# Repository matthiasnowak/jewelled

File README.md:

# JewelLED / LuxAura Earring

These stylish earrings have 18 small LEDs on them, which can light up in any pattern. A microphone allows for the potential to sync the patterns up to music. The whole earring is powered off a regular coin cell battery, and can even be used with lithium rechargeable coin cells! It runs around 10-12h at moderate animation load and brightness of a LIR2032 rechargeable Lithium battery

A seperate charging and programming board allows to interface the earrings with your PC, gives you simple access to the programming pin of the earrings and can be used to charge them up if used with lithium rechargeable coin cells.

## Hardware Overview:

### LuxAura 01:

- WCH CH32V203G6U6 microcontroller
- 18 LEDs 0603, single color
- CR2032 battery holder
- optional LIR2032 charging and protection circuit
- Operating at 2.7V, allowing for low battery voltage operation
- 2 buttons and a power switch
- buzzer for audio user feedback
- microphone, which can be used for music detection

### LuxCharge:

- TBD

## Software

Software is currently WIP. The charging board can activate/deactivate 5V charging voltage to the earrings and can rudimentely detect their presence.
The earring software can show basic animations and cycle between them. Test code for microphone sampling is running, but currently beat detection doesnt work.

## Ressources and other notes

- Images, schematics and PCB plots can be found in the "res" folder.
- Development is published here, issues are used for internal issue and project tracking. Feel free to contribute
- The PCBs can be ordered through Turnkey PCBA providers like JLCPCB.

## License

The attached LICENSE.md file contains information about the license.

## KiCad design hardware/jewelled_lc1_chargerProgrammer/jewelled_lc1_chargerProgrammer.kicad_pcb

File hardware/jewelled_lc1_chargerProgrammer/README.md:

# LuxAura LuxCharger Hardware

## Hardware Overview

- WIP

## Notes

- WIP
- Please note the correct jumper settings to allow communications or setting pullup/down resistors

## Images

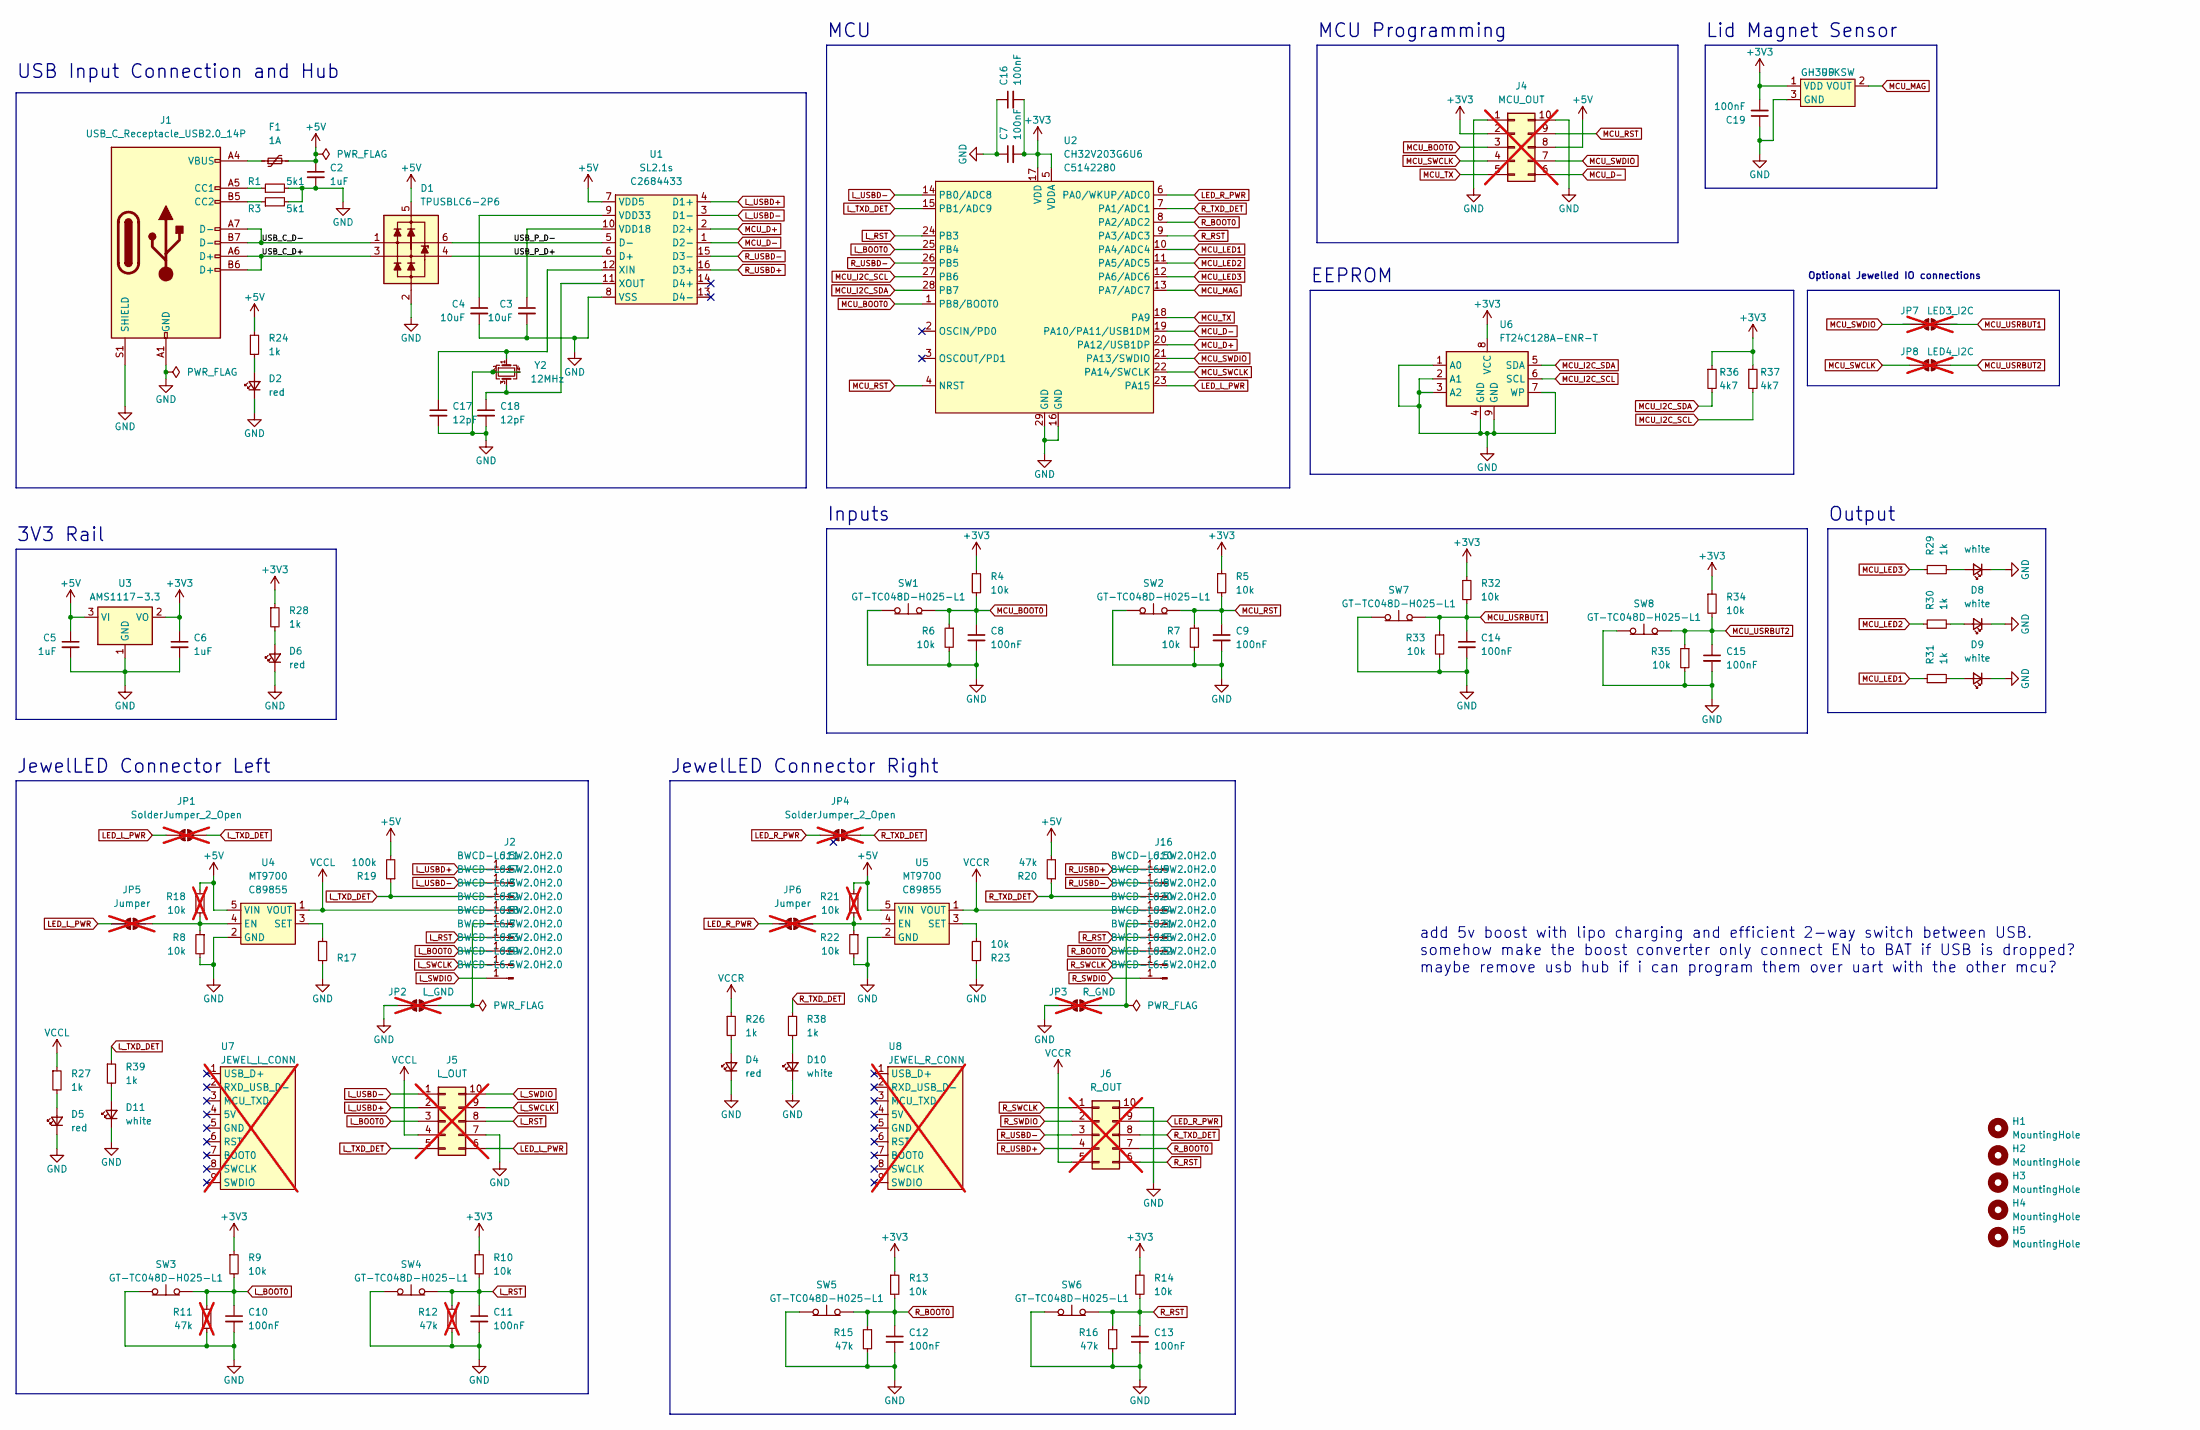
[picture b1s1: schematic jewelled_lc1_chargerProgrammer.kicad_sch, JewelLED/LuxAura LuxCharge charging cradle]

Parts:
C2, C5, C6: 1uF; C_0603_1608Metric; MPN C15849; LCSC C15849
C3, C4: 10uF; C_0805_2012Metric; MPN C19702; LCSC C19702
C7, C8, C9, C10, C11, C12, C13, C14, C15, C16, C19: 100nF; C_0603_1608Metric; MPN C14663; LCSC C14663
C17, C18: 12pF; C_0603_1608Metric; MPN C38523; LCSC C38523
D1: TPUSBLC6-2P6; SOT-666; MPN C2682291; LCSC C2682291
D2, D4, D5, D6: red; LED_0603_1608Metric; MPN C2286; LCSC C2286
D7, D8, D9, D10, D11: white; LED_0603_1608Metric; MPN C2290; LCSC C2290
F1: 1A; Fuse_1210_3225Metric; MPN C692151; LCSC C692151
H1, H2, H3, H4, H5: MountingHole; Mounting_Sinhoo-M2_H2mm_SMTSO2020MTJ; MPN C2916384; LCSC C2916384
J1: USB_C_Receptacle_USB2.0_14P; USB_C_Receptacle_GT-USB-7010B; MPN C2988369; LCSC C2988369
J2, J3, J7, J8, J9, J10, J11, J12, J13, J14, J15, J16, J17, J18, J19, J20, J21, J22: BWCD-L6.5W2.0H2.0; jewelled_2mm_pogopad; MPN C2826552; LCSC C2826552
J4: MCU_OUT; pogoheader_2x05_1.5mm; MPN x; not fitted
J5: L_OUT; pogoheader_2x05_1.5mm; MPN x; not fitted
J6: R_OUT; pogoheader_2x05_1.5mm; MPN x; not fitted
JP1, JP4: SolderJumper_2_Open; SolderJumper-2_P1.3mm_Open_RoundedPad1.0x1.5mm; MPN x; not fitted
JP2: L_GND; SolderJumper-2_P1.3mm_Open_RoundedPad1.0x1.5mm; MPN x; not fitted
JP3: R_GND; SolderJumper-2_P1.3mm_Open_RoundedPad1.0x1.5mm; MPN x; not fitted
JP5, JP6: Jumper; SolderJumper-2_P1.3mm_Open_RoundedPad1.0x1.5mm; MPN x; not fitted
JP7: LED3_I2C; SolderJumper-2_P1.3mm_Open_RoundedPad1.0x1.5mm; MPN x; not fitted
JP8: LED4_I2C; SolderJumper-2_P1.3mm_Open_RoundedPad1.0x1.5mm; MPN x; not fitted
R1, R3: 5k1; R_0603_1608Metric; MPN C23186; LCSC C23186
R4, R5, R6, R7, R8, R9, R10, R13, R14, R17, R22, R23, R32, R33, R34, R35: 10k; R_0603_1608Metric; MPN C25804; LCSC C25804
R11, R12: 47k; R_0603_1608Metric; MPN C25819; LCSC C25819; not fitted
R15, R16, R20: 47k; R_0603_1608Metric; MPN C25819; LCSC C25819
R18, R21: 10k; R_0603_1608Metric; MPN C25804; LCSC C25804; not fitted
R19: 100k; R_0603_1608Metric; MPN C25803; LCSC C25803
R24, R26, R27, R28, R29, R30, R31, R38, R39: 1k; R_0603_1608Metric; MPN C21190; LCSC C21190
R36, R37: 4k7; R_0603_1608Metric; MPN C23162; LCSC C23162
SW1, SW2, SW3, SW4, SW5, SW6, SW7, SW8: GT-TC048D-H025-L1; MPN C843674; LCSC C843674
U1: SL2.1s; SSOP16_SL2.1S; MPN C2684433; LCSC C2684433
U2: CH32V203G6U6; QFN-28-1EP_4x4mm_P0.4mm_EP2.6x2.6mm; MPN C5142280; LCSC C5142280
U3: AMS1117-3.3; SOT-89-3; MPN C18723569; LCSC C18723569
U4, U5: MT9700; SOT-23-5; MPN C89855; LCSC C89855
U6: FT24C128A-ENR-T; DFN-8-1EP_3x2mm_P0.5mm_EP1.7x1.6mm; MPN C232872; LCSC C232872
U7: JEWEL_L_CONN; jewelled_lc1_v1_conn; MPN C2826552; LCSC C2826552; not fitted
U8: JEWEL_R_CONN; jewelled_lc1_v1_conn; MPN C2826552; LCSC C2826552; not fitted
U9: GH39FKSW; SOT-23-3; MPN C266230; LCSC C266230
Y2: 12MHz; Crystal_SMD_2520-4Pin_2.5x2.0mm; MPN C5122639; LCSC C5122639

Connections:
+3V3: C6.1, C7.2, C16.2, C19.2, J4.2, R4.1, R5.1, R9.1, R10.1, R13.1, R14.1, R28.1, R32.1, R34.1, R36.1, R37.1, U2.5 (VDDA), U2.17 (VDD), U3.2 (VO), U6.8 (VCC), U9.1 (VDD)
+5V: C2.1, C5.1, D1.5 (VP), F1.2, J4.8, R18.1, R19.2, R20.2, R21.1, R24.1, U1.7 (VDD5), U3.3 (VI), U4.5 (VIN), U5.5 (VIN)
/USB_C_D+: D1.3 (L2), J1.A6 (D+), J1.B6 (D+)
/USB_C_D-: D1.1 (L1), J1.A7 (D-), J1.B7 (D-)
/USB_P_D+: D1.4 (L2), U1.6 (D+)
/USB_P_D-: D1.6 (L1), U1.5 (D-)
GND: C2.2, C3.2, C4.2, C5.2, C6.2, C7.1, C8.2, C9.2, C10.2, C11.2, C12.2, C13.2, C14.2, C15.2, C16.1, C17.2, C18.2, C19.1, D1.2 (VN), D2.1 (K), D4.1 (K), D5.1 (K), D6.1 (K), D7.1 (K), D8.1 (K), D9.1 (K), D10.1 (K), D11.1 (K), J1.A1 (GND), J1.A12 (GND), J1.B1 (GND), J1.B12 (GND), J1.S1 (SHIELD), J4.1, J4.10, J5.7, J6.10, JP2.2 (B), JP3.2 (B), R1.2, R3.2, R6.2, R7.2, R8.2, R11.2, R12.2, R15.2, R16.2, R17.1, R22.2, R23.1, R33.2, R35.2, SW1.1 (A), SW2.1 (A), SW3.1 (A), SW4.1 (A), SW5.1 (A), SW6.1 (A), SW7.1 (A), SW8.1 (A), U1.8 (VSS), U2.16 (GND), U2.29 (GND), U3.1 (GND), U4.2 (GND), U5.2 (GND), U6.1 (A0), U6.2 (A1), U6.3 (A2), U6.4 (GND), U6.7 (WP), U6.9 (GND), U9.3 (GND), Y2.2, Y2.4
LED_L_PWR: J5.6, JP1.1 (A), JP5.1 (A), U2.23 (PA15)
LED_R_PWR: J6.9, JP4.1 (A), JP6.1 (A), U2.6 (PA0/WKUP/ADC0)
L_BOOT0: C10.1, J5.3, J7.1, R9.2, R11.1, SW3.2 (B), U2.25 (PB4)
L_RST: C11.1, J5.8, J18.1, R10.2, R12.1, SW4.2 (B), U2.24 (PB3)
L_SWCLK: J5.9, J13.1
L_SWDIO: J5.10, J19.1
L_TXD_DET: J5.5, J17.1, JP1.2 (B), R19.1, R39.1, U2.15 (PB1/ADC9)
L_USBD+: J2.1, J5.2, U1.4 (D1+)
L_USBD-: J5.1, J11.1, U1.3 (D1-), U2.14 (PB0/ADC8)
MCU_BOOT0: C8.1, J4.3, R4.2, R6.1, SW1.2 (B), U2.1 (PB8/BOOT0)
MCU_D+: U1.2 (D2+), U2.20 (PA12/USB1DP)
MCU_D-: J4.6, U1.1 (D2-), U2.19 (PA10/PA11/USB1DM)
MCU_I2C_SCL: R37.2, U2.27 (PB6), U6.6 (SCL)
MCU_I2C_SDA: R36.2, U2.28 (PB7), U6.5 (SDA)
MCU_LED1: R31.1, U2.10 (PA4/ADC4)
MCU_LED2: R30.1, U2.11 (PA5/ADC5)
MCU_LED3: R29.1, U2.12 (PA6/ADC6)
MCU_MAG: U2.13 (PA7/ADC7), U9.2 (VOUT)
MCU_RST: C9.1, J4.9, R5.2, R7.1, SW2.2 (B), U2.4 (NRST)
MCU_SWCLK: J4.4, JP8.2 (B), U2.22 (PA14/SWCLK)
MCU_SWDIO: J4.7, JP7.2 (B), U2.21 (PA13/SWDIO)
MCU_TX: J4.5, U2.18 (PA9)
MCU_USRBUT1: C14.1, JP7.1 (A), R32.2, R33.1, SW7.2 (B)
MCU_USRBUT2: C15.1, JP8.1 (A), R34.2, R35.1, SW8.2 (B)
unnamed: D2.2 (A), R24.2
unnamed: D4.2 (A), R26.2
unnamed: D5.2 (A), R27.2
unnamed: D6.2 (A), R28.2
unnamed: D7.2 (A), R29.2
unnamed: D8.2 (A), R30.2
unnamed: D9.2 (A), R31.2
unnamed: D10.2 (A), R38.2
unnamed: D11.2 (A), R39.2
unnamed: F1.1, J1.A4 (VBUS), J1.A9 (VBUS), J1.B4 (VBUS), J1.B9 (VBUS)
unnamed: J1.A5 (CC1), R1.1
unnamed: J1.B5 (CC2), R3.1
unnamed: J12.1, JP2.1 (A)
unnamed: J20.1, JP3.1 (A)
unnamed: JP5.2 (B), R8.1, R18.2, U4.4 (EN)
unnamed: JP6.2 (B), R21.2, R22.1, U5.4 (EN)
unnamed: C3.1, U1.10 (VDD18)
unnamed: C4.1, U1.9 (VDD33)
unnamed: C17.1, U1.12 (XIN), Y2.1
unnamed: C18.1, U1.11 (XOUT), Y2.3
unnamed: R17.2, U4.3 (SET)
unnamed: R23.2, U5.3 (SET)
R_BOOT0: C12.1, J6.7, J21.1, R13.2, R15.1, SW5.2 (B), U2.8 (PA2/ADC2)
R_RST: C13.1, J6.6, J14.1, R14.2, R16.1, SW6.2 (B), U2.9 (PA3/ADC3)
R_SWCLK: J6.1, J15.1
R_SWDIO: J6.2, J22.1
R_TXD_DET: J6.8, J9.1, JP4.2 (B), R20.1, R38.1, U2.7 (PA1/ADC1)
R_USBD+: J6.4, J16.1, U1.16 (D3+)
R_USBD-: J6.3, J10.1, U1.15 (D3-), U2.26 (PB5)
VCCL: J3.1, J5.4, R27.1, U4.1 (VOUT)
VCCR: J6.5, J8.1, R26.1, U5.1 (VOUT)

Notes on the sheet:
3V3 Rail
JewelLED Connector Left
JewelLED Connector Right
EEPROM
Optional Jewelled IO connections
Inputs
USB Input Connection and Hub
MCU
MCU Programming
add 5v boost with lipo charging and efficient 2-way switch between USB. somehow make the boost converter only connect EN to BAT if USB is dropped? maybe remove usb hub if i can program them over uart with the other mcu?
Lid Magnet Sensor
Output

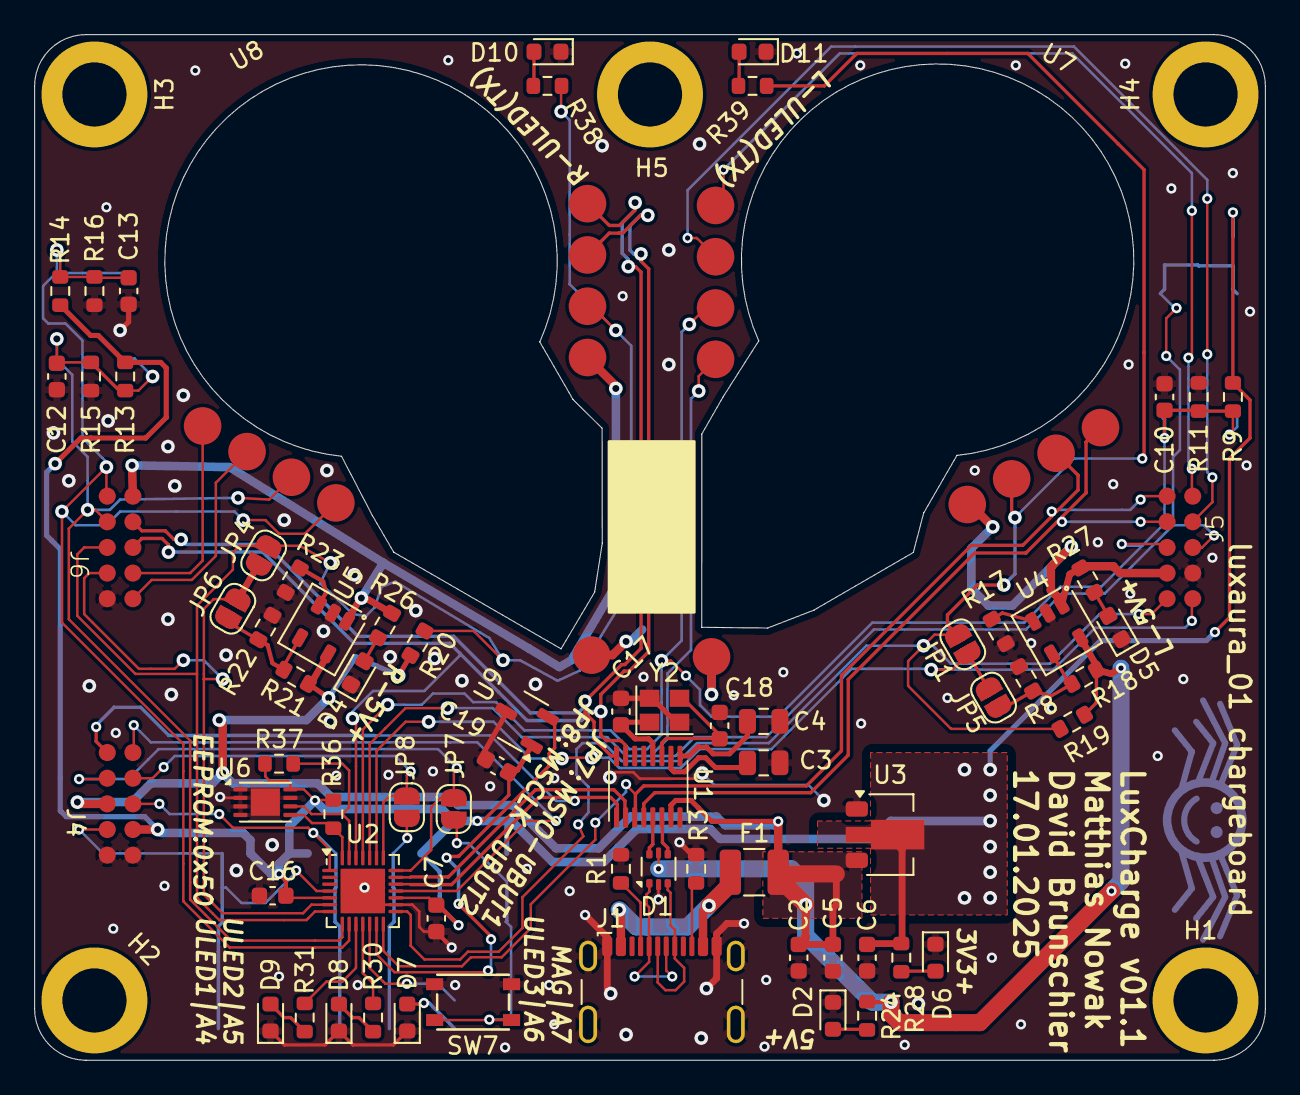
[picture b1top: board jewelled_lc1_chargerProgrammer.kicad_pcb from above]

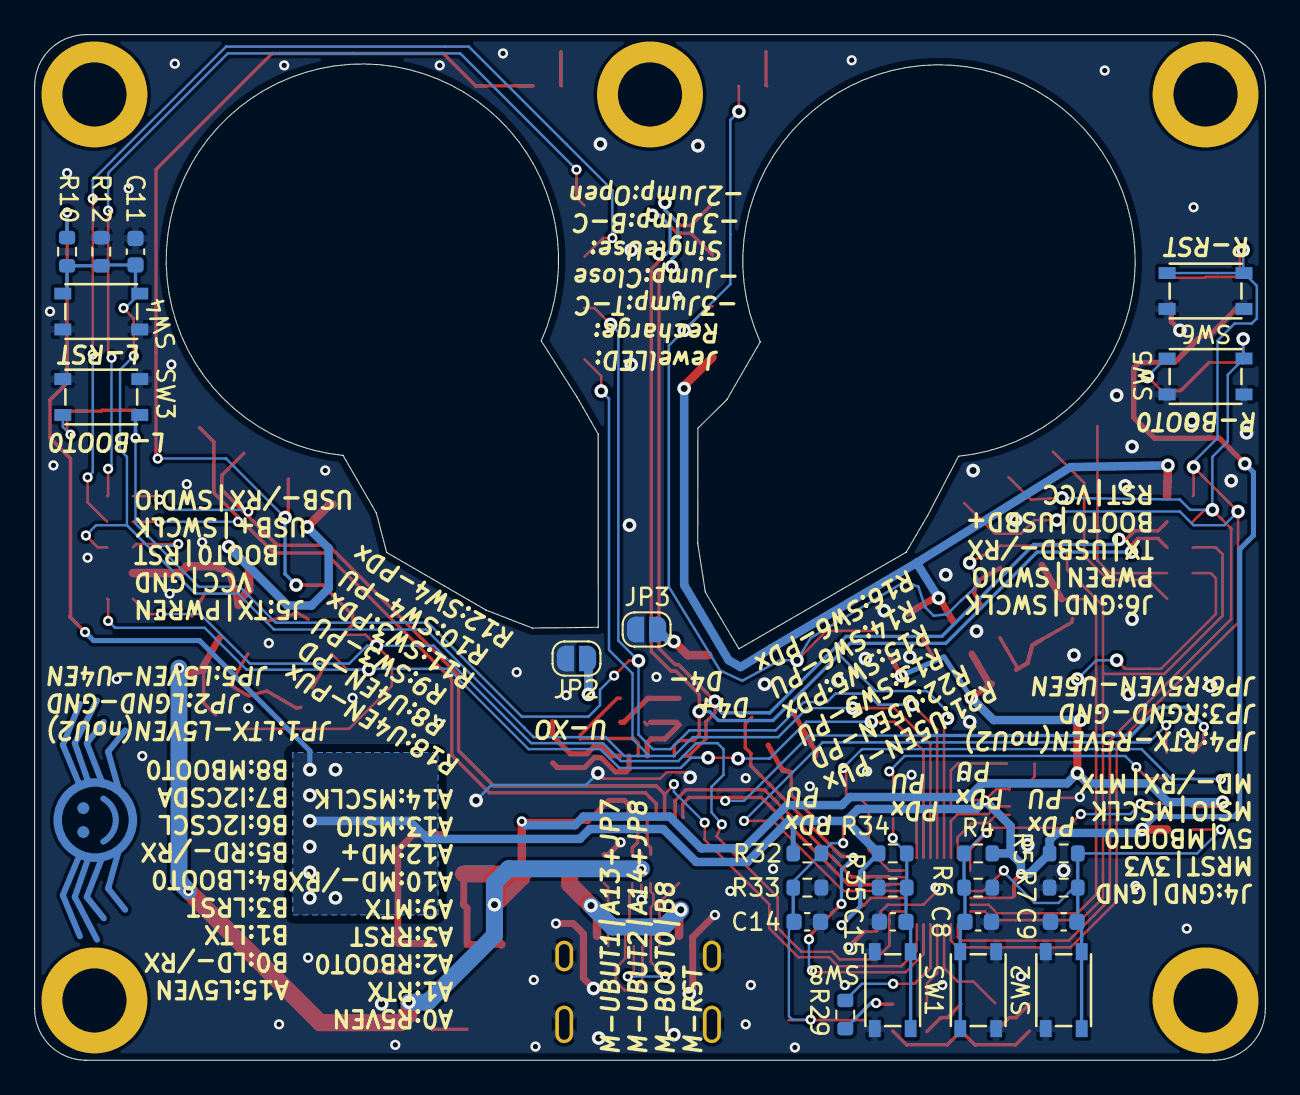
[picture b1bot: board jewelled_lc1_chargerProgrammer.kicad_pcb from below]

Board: 2 copper layers, 72.0 x 60.0 mm, 119 parts (25 on the bottom side), 62 nets.

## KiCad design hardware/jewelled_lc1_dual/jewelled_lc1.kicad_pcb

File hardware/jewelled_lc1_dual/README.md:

# LuxAura 01 Dual Earring Hardware

## Notes

This is a panel meant for production of the Earrings, allowing for 2 Earrings per panel.

## Images

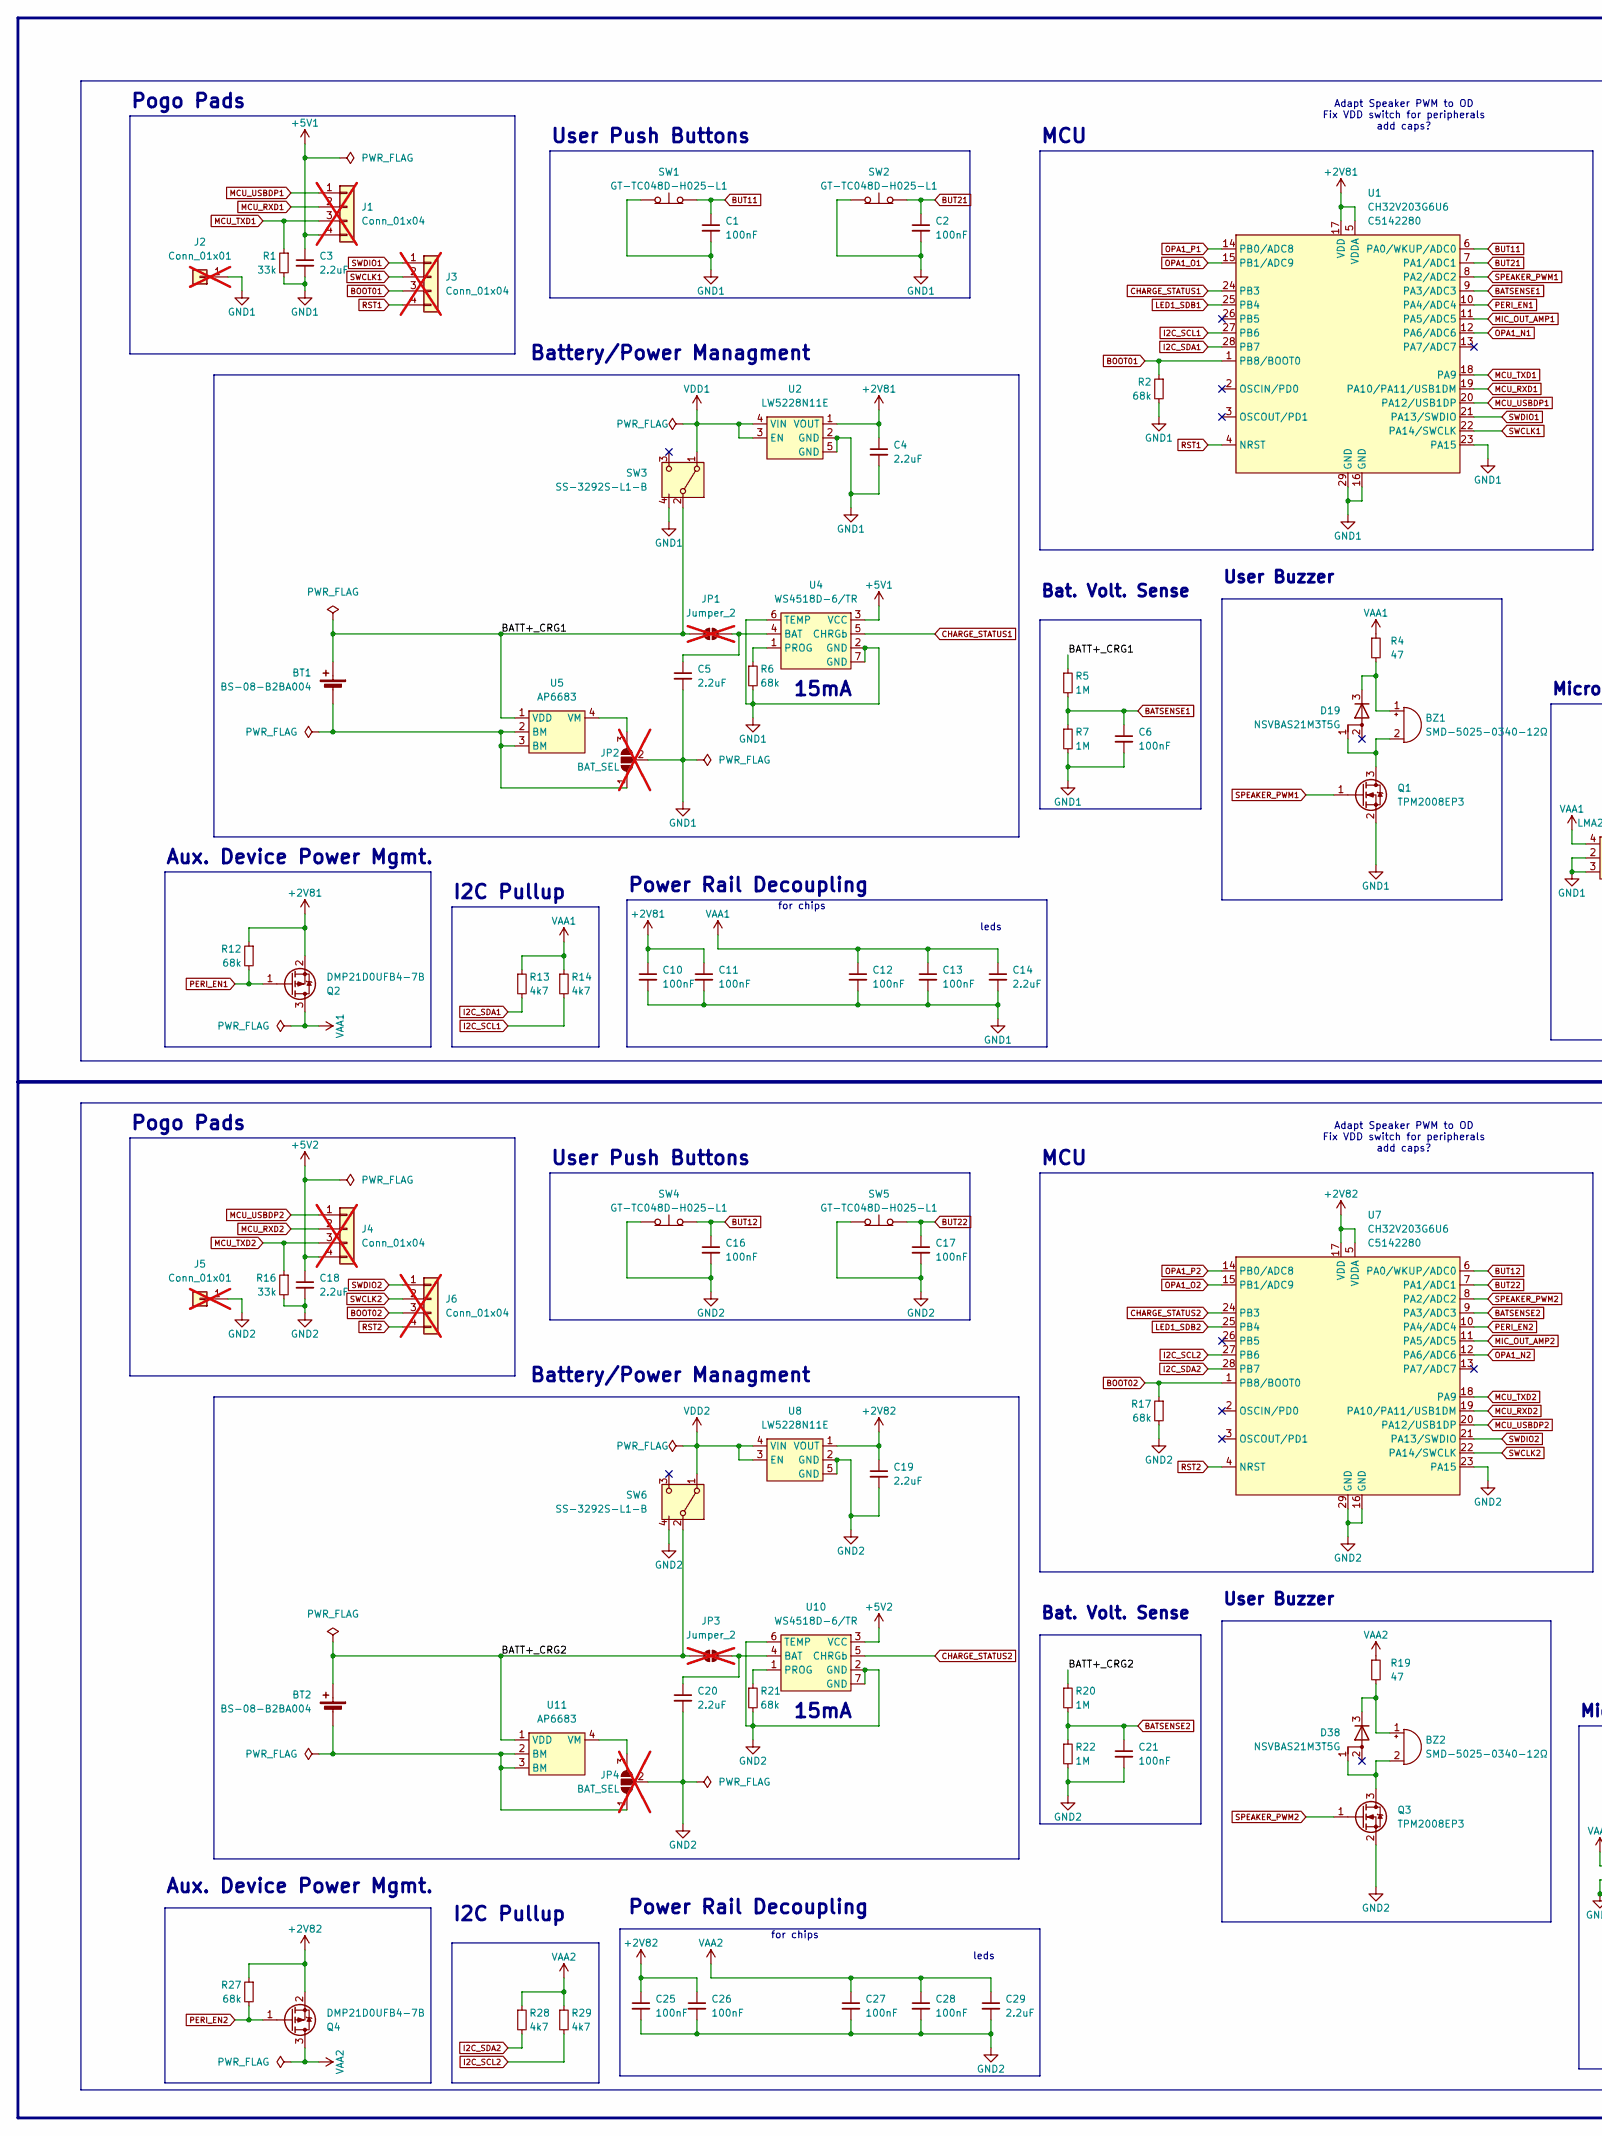
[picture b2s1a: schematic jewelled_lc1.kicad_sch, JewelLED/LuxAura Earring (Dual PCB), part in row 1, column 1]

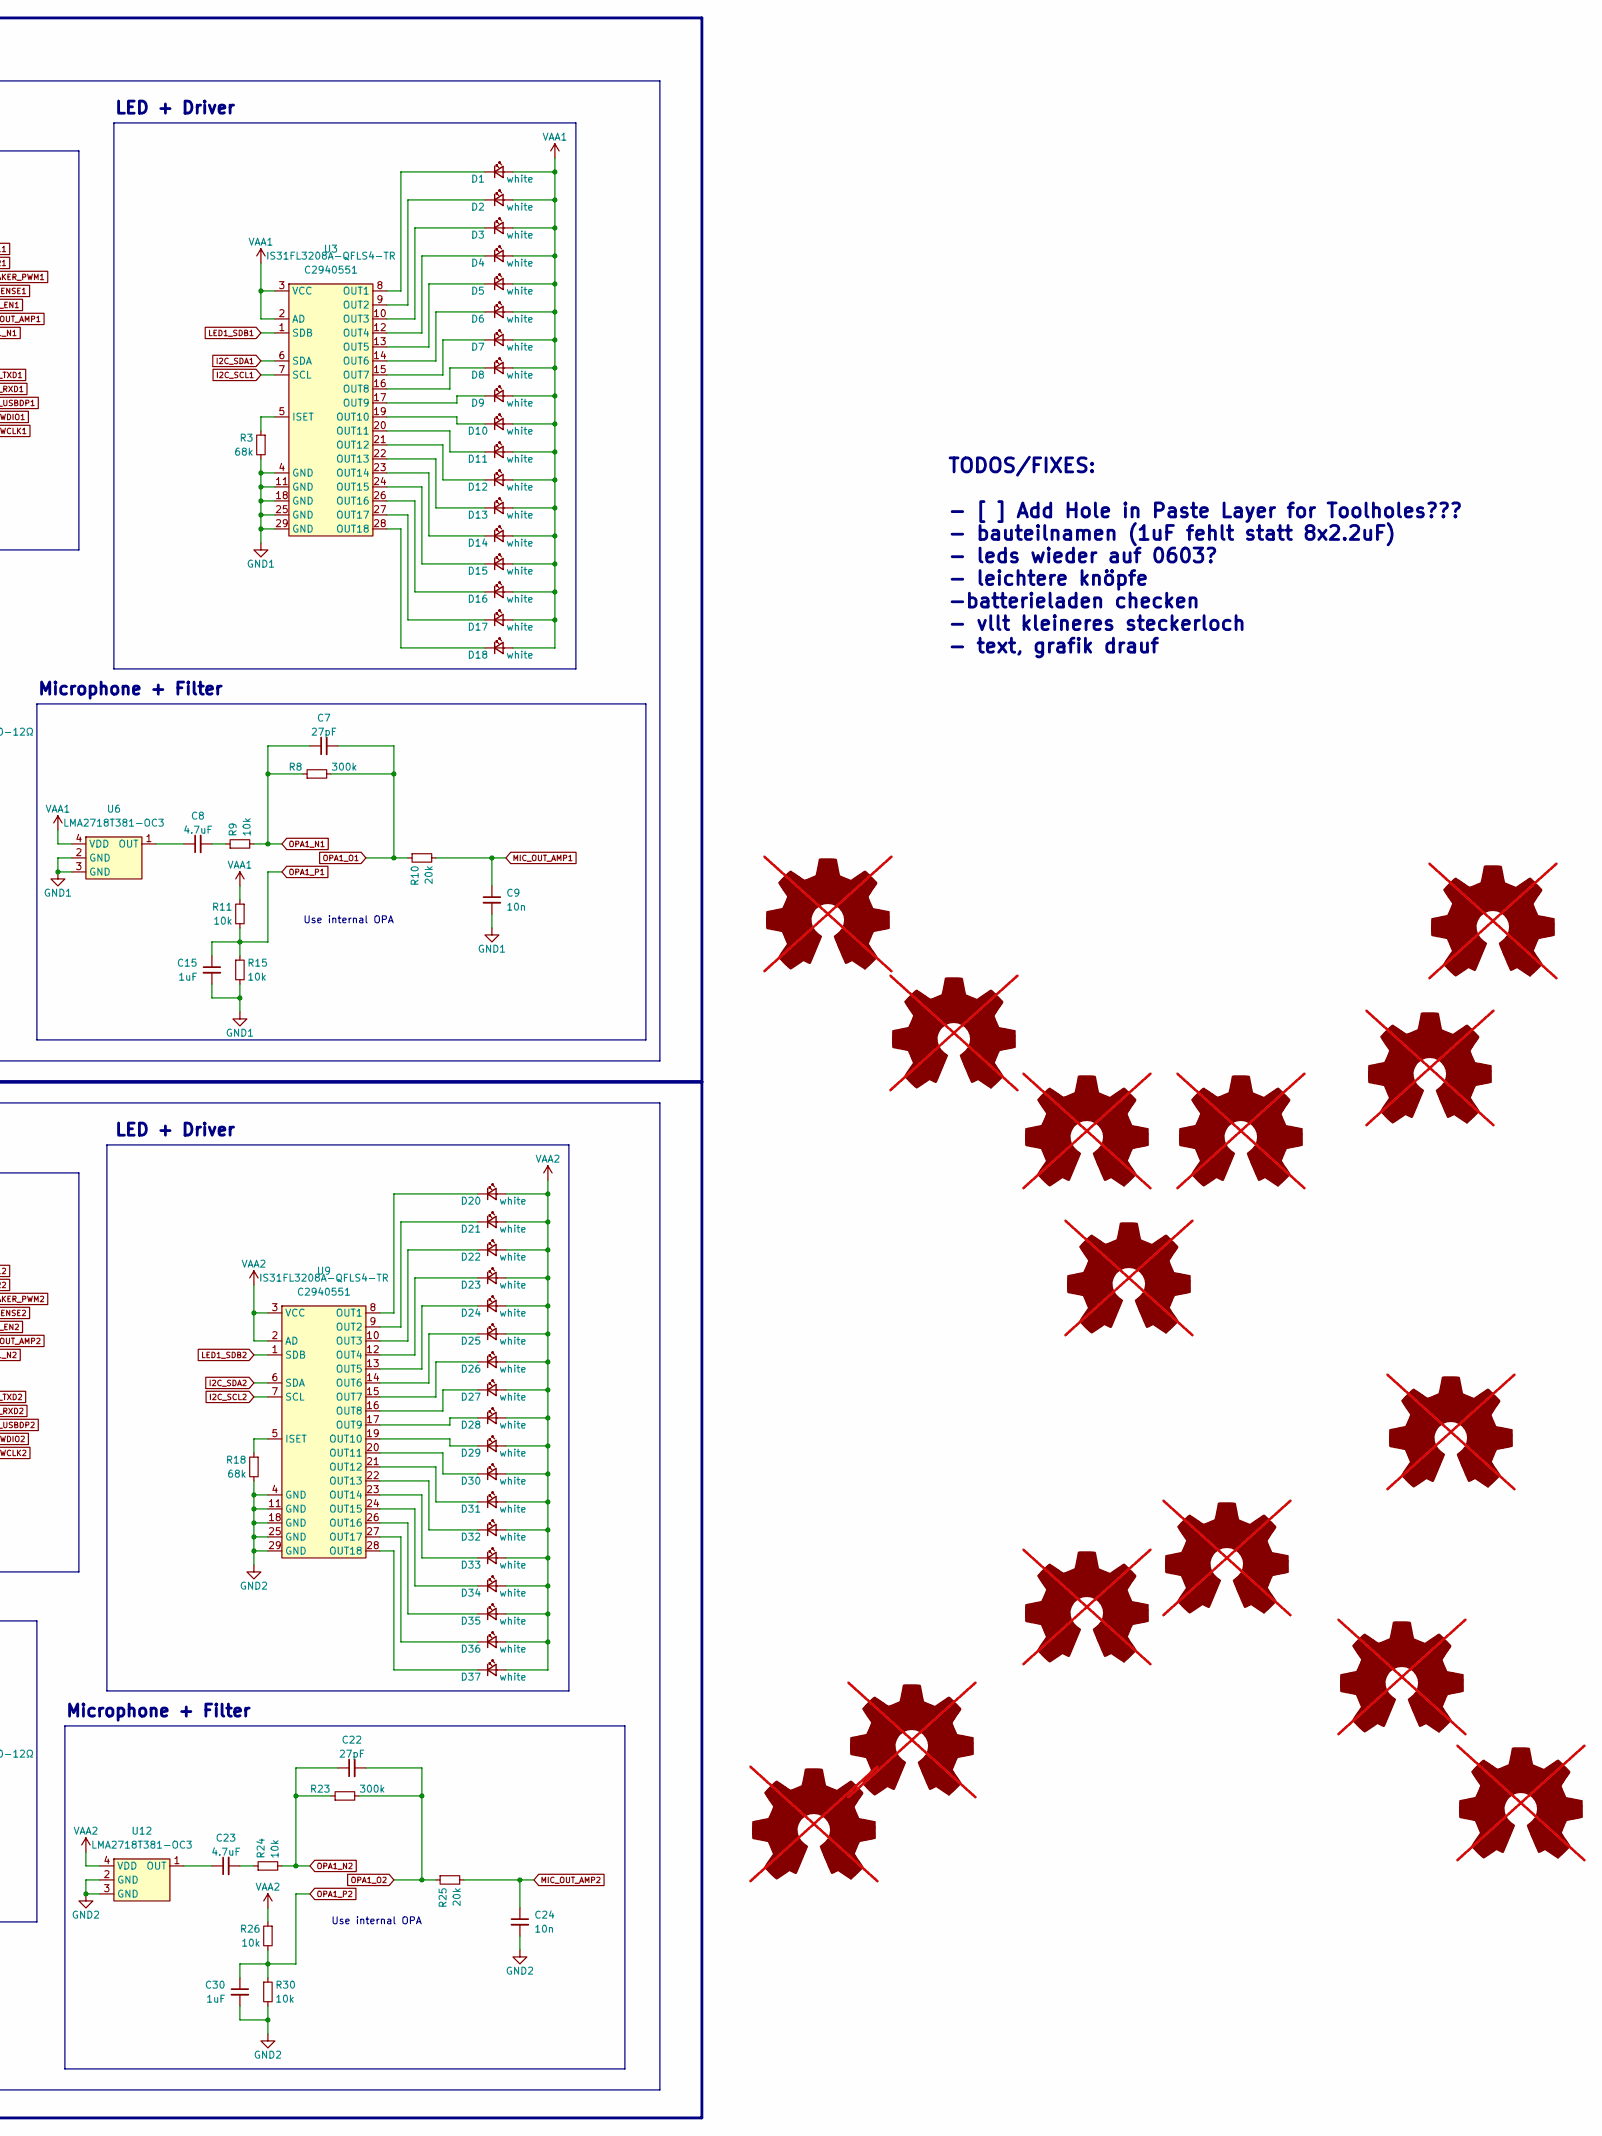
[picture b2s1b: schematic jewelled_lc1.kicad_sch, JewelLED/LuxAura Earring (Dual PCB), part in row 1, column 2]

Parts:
BT1, BT2: BS-08-B2BA004; MPN C964780; LCSC C964780
BZ1, BZ2: SMD-5025-0340-12Ω; SMD-5025-0340; MPN C2693575; LCSC C2693575
C1, C2, C6, C10, C11, C12, C13, C16, C17, C21, C25, C26, C27, C28: 100nF; C_0402_1005Metric; MPN C1525; LCSC C1525
C3, C4, C5, C14, C18, C19, C20, C29: 2.2uF; C_0402_1005Metric; MPN C12530; LCSC C12530
C7, C22: 27pF; C_0402_1005Metric; MPN C1557; LCSC C1557
C8, C23: 4.7uF; C_0402_1005Metric; MPN C23733; LCSC C23733
C9, C24: 10n; C_0402_1005Metric; MPN C15195; LCSC C15195
C15, C30: 1uF; C_0402_1005Metric; MPN C52923; LCSC C52923
D1, D2, D3, D4, D5, D6, D7, D8, D9, D10, D11, D12, D13, D14, D15, D16, D17, D18, D20, D21, D22, D23, D24, D25, D26, D27, D28, D29, D30, D31, D32, D33, D34, D35, D36, D37: white; LED_0402_1005Metric; MPN C157742; LCSC C157742
D19, D38: NSVBAS21M3T5G; SOT-723; MPN C896450; LCSC C896450
J1, J3, J4, J6: Conn_01x04; pogo_conn_01x03_P2.0mm_angled; not fitted
J2, J5: Conn_01x01; pogo_conn_01x01_P2.0mm; not fitted
JP1, JP3: Jumper_2; SolderJumper-2_P1.3mm_Open_RoundedPad1.0x1.5mm_NoSilk; not fitted
JP2, JP4: BAT_SEL; SolderJumper-3_P1.3mm_Open_RoundedPad1.0x1.5mm_NoSilk; not fitted
Q1, Q3: TPM2008EP3; DFN-3_1.0x0.6mm_P0.35mm; MPN C2682293; LCSC C2682293
Q2, Q4: DMP21D0UFB4-7B; DFN-3_1.0x0.6mm_P0.35mm; MPN C155329; LCSC C155329
R1, R16: 33k; R_0402_1005Metric; MPN C25779; LCSC C25779
R2, R3, R6, R12, R17, R18, R21, R27: 68k; R_0402_1005Metric; MPN C36871; LCSC C36871
R4, R19: 47; R_0402_1005Metric; MPN C25118; LCSC C25118
R5, R7, R20, R22: 1M; R_0402_1005Metric; MPN C26083; LCSC C26083
R8, R23: 300k; R_0402_1005Metric; MPN C25774; LCSC C25774
R9, R11, R15, R24, R26, R30: 10k; R_0402_1005Metric; MPN C25744; LCSC C25744
R10, R25: 20k; R_0402_1005Metric; MPN C25765; LCSC C25765
R13, R14, R28, R29: 4k7; R_0402_1005Metric; MPN C25900; LCSC C25900
SW1, SW2, SW4, SW5: GT-TC048D-H025-L1; MPN C843674; LCSC C843674
SW3, SW6: SS-3292S-L1-B; MPN C397350; LCSC C397350
SYM1, SYM2, SYM13, SYM14: jlcpcb_toolhole; not fitted
SYM3, SYM4, SYM11, SYM12: jlcpcb_fiducial; Fiducial_1mm_Mask2mm; not fitted
SYM5, SYM6, SYM9, SYM10: mousebite_outer; not fitted
SYM7, SYM8: mousebite_inner; not fitted
U1, U7: CH32V203G6U6; QFN-28-1EP_4x4mm_P0.4mm_EP2.6x2.6mm; MPN C5142280; LCSC C5142280
U2, U8: LW5228N11E; UDFN-4-1EP_1x1mm_P0.65mm_EP0.48x0.48mm; MPN C20630428; LCSC C20630428
U3, U9: IS31FL3208A-QFLS4-TR; QFN-28-1EP_4x4mm_P0.4mm_EP2.4x2.4mm; MPN C2940551; LCSC C2940551
U4, U10: WS4518D-6/TR; DFN-6-1EP_2x2mm_P0.65mm_EP1x1.6mm; MPN C910991; LCSC C910991
U5, U11: AP6683; UDFN-4-1EP_1x1mm_P0.65mm_EP0.48x0.48mm; MPN C2849565; LCSC C2849565
U6: LMA2718T381-OC3; ZTS6117H; MPN C2999748; LCSC C2999748
U12: LMA2718T381-OC3; ZTS6117H; MPN C19267420; LCSC C2999748

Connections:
+2V81: C4.1, C10.1, C11.1, Q2.2 (S), R12.1, U1.5 (VDDA), U1.17 (VDD), U2.1 (VOUT)
+2V82: C19.1, C25.1, C26.1, Q4.2 (S), R27.1, U7.5 (VDDA), U7.17 (VDD), U8.1 (VOUT)
+5V1: C3.1, J1.4, U4.3 (VCC)
+5V2: C18.1, J4.4, U10.3 (VCC)
/BATT+_CRG1: BT1.1 (+), JP1.1 (A), R5.1, SW3.2 (B), U5.1 (VDD)
/BATT+_CRG2: BT2.1 (+), JP3.1 (A), R20.1, SW6.2 (B), U11.1 (VDD)
BATSENSE1: C6.1, R5.2, R7.1, U1.9 (PA3/ADC3)
BATSENSE2: C21.1, R20.2, R22.1, U7.9 (PA3/ADC3)
BOOT01: J3.3, R2.1, U1.1 (PB8/BOOT0)
BOOT02: J6.3, R17.1, U7.1 (PB8/BOOT0)
BUT11: C1.1, SW1.2 (B), U1.6 (PA0/WKUP/ADC0)
BUT12: C16.1, SW4.2 (B), U7.6 (PA0/WKUP/ADC0)
BUT21: C2.1, SW2.2 (B), U1.7 (PA1/ADC1)
BUT22: C17.1, SW5.2 (B), U7.7 (PA1/ADC1)
CHARGE_STATUS1: U1.24 (PB3), U4.5 (CHRGb)
CHARGE_STATUS2: U7.24 (PB3), U10.5 (CHRGb)
GND1: C1.2, C2.2, C3.2, C4.2, C5.2, C6.2, C9.2, C10.2, C11.2, C12.2, C13.2, C14.2, C15.2, J2.1, JP2.2 (C), Q1.2 (S), R1.2, R2.2, R3.2, R6.2, R7.2, R15.2, SW1.1 (A), SW2.1 (A), SW3.4 (B), U1.16 (GND), U1.23 (PA15), U1.29 (GND), U2.2 (GND), U2.5 (GND), U3.4 (GND), U3.11 (GND), U3.18 (GND), U3.25 (GND), U3.29 (GND), U4.2 (GND), U4.6 (TEMP), U4.7 (GND), U6.2 (GND), U6.3 (GND)
GND2: C16.2, C17.2, C18.2, C19.2, C20.2, C21.2, C24.2, C25.2, C26.2, C27.2, C28.2, C29.2, C30.2, J5.1, JP4.2 (C), Q3.2 (S), R16.2, R17.2, R18.2, R21.2, R22.2, R30.2, SW4.1 (A), SW5.1 (A), SW6.4 (B), U7.16 (GND), U7.23 (PA15), U7.29 (GND), U8.2 (GND), U8.5 (GND), U9.4 (GND), U9.11 (GND), U9.18 (GND), U9.25 (GND), U9.29 (GND), U10.2 (GND), U10.6 (TEMP), U10.7 (GND), U12.2 (GND), U12.3 (GND)
I2C_SCL1: R14.2, U1.27 (PB6), U3.7 (SCL)
I2C_SCL2: R29.2, U7.27 (PB6), U9.7 (SCL)
I2C_SDA1: R13.2, U1.28 (PB7), U3.6 (SDA)
I2C_SDA2: R28.2, U7.28 (PB7), U9.6 (SDA)
LED1_SDB1: U1.25 (PB4), U3.1 (SDB)
LED1_SDB2: U7.25 (PB4), U9.1 (SDB)
MCU_RXD1: J1.2, U1.19 (PA10/PA11/USB1DM)
MCU_RXD2: J4.2, U7.19 (PA10/PA11/USB1DM)
MCU_TXD1: J1.3, R1.1, U1.18 (PA9)
MCU_TXD2: J4.3, R16.1, U7.18 (PA9)
MCU_USBDP1: J1.1, U1.20 (PA12/USB1DP)
MCU_USBDP2: J4.1, U7.20 (PA12/USB1DP)
MIC_OUT_AMP1: C9.1, R10.2, U1.11 (PA5/ADC5)
MIC_OUT_AMP2: C24.1, R25.2, U7.11 (PA5/ADC5)
unnamed: BT1.2 (-), JP2.1 (A), U5.2 (BM), U5.3 (BM)
unnamed: BT2.2 (-), JP4.1 (A), U11.2 (BM), U11.3 (BM)
unnamed: BZ1.1 (+), D19.3 (K), R4.2
unnamed: BZ1.2 (-), D19.1 (A), Q1.3 (D)
unnamed: BZ2.1 (+), D38.3 (K), R19.2
unnamed: BZ2.2 (-), D38.1 (A), Q3.3 (D)
unnamed: C8.2, R9.1
unnamed: C23.2, R24.1
unnamed: D1.1 (K), U3.8 (OUT1)
unnamed: D2.1 (K), U3.9 (OUT2)
unnamed: D3.1 (K), U3.10 (OUT3)
unnamed: D4.1 (K), U3.12 (OUT4)
unnamed: D5.1 (K), U3.13 (OUT5)
unnamed: D6.1 (K), U3.14 (OUT6)
unnamed: D7.1 (K), U3.15 (OUT7)
unnamed: D8.1 (K), U3.16 (OUT8)
unnamed: D9.1 (K), U3.17 (OUT9)
unnamed: D10.1 (K), U3.19 (OUT10)
unnamed: D11.1 (K), U3.20 (OUT11)
unnamed: D12.1 (K), U3.21 (OUT12)
unnamed: D13.1 (K), U3.22 (OUT13)
unnamed: D14.1 (K), U3.23 (OUT14)
unnamed: D15.1 (K), U3.24 (OUT15)
unnamed: D16.1 (K), U3.26 (OUT16)
unnamed: D17.1 (K), U3.27 (OUT17)
unnamed: D18.1 (K), U3.28 (OUT18)
unnamed: D20.1 (K), U9.8 (OUT1)
unnamed: D21.1 (K), U9.9 (OUT2)
unnamed: D22.1 (K), U9.10 (OUT3)
unnamed: D23.1 (K), U9.12 (OUT4)
unnamed: D24.1 (K), U9.13 (OUT5)
unnamed: D25.1 (K), U9.14 (OUT6)
unnamed: D26.1 (K), U9.15 (OUT7)
unnamed: D27.1 (K), U9.16 (OUT8)
unnamed: D28.1 (K), U9.17 (OUT9)
unnamed: D29.1 (K), U9.19 (OUT10)
unnamed: D30.1 (K), U9.20 (OUT11)
unnamed: D31.1 (K), U9.21 (OUT12)
unnamed: D32.1 (K), U9.22 (OUT13)
unnamed: D33.1 (K), U9.23 (OUT14)
unnamed: D34.1 (K), U9.24 (OUT15)
unnamed: D35.1 (K), U9.26 (OUT16)
unnamed: D36.1 (K), U9.27 (OUT17)
unnamed: D37.1 (K), U9.28 (OUT18)
unnamed: C5.1, JP1.2 (B), U4.4 (BAT)
unnamed: JP2.3 (B), U5.4 (VM)
unnamed: C20.1, JP3.2 (B), U10.4 (BAT)
unnamed: JP4.3 (B), U11.4 (VM)
unnamed: R3.1, U3.5 (ISET)
unnamed: R6.1, U4.1 (PROG)
unnamed: C8.1, U6.1 (OUT)
unnamed: R18.1, U9.5 (ISET)
unnamed: R21.1, U10.1 (PROG)
unnamed: C23.1, U12.1 (OUT)
OPA1_N1: C7.1, R8.1, R9.2, U1.12 (PA6/ADC6)
OPA1_N2: C22.1, R23.1, R24.2, U7.12 (PA6/ADC6)
OPA1_O1: C7.2, R8.2, R10.1, U1.15 (PB1/ADC9)
OPA1_O2: C22.2, R23.2, R25.1, U7.15 (PB1/ADC9)
OPA1_P1: C15.1, R11.2, R15.1, U1.14 (PB0/ADC8)
OPA1_P2: C30.1, R26.2, R30.1, U7.14 (PB0/ADC8)
PERI_EN1: Q2.1 (G), R12.2, U1.10 (PA4/ADC4)
PERI_EN2: Q4.1 (G), R27.2, U7.10 (PA4/ADC4)
RST1: J3.4, U1.4 (NRST)
RST2: J6.4, U7.4 (NRST)
SPEAKER_PWM1: Q1.1 (G), U1.8 (PA2/ADC2)
SPEAKER_PWM2: Q3.1 (G), U7.8 (PA2/ADC2)
SWCLK1: J3.2, U1.22 (PA14/SWCLK)
SWCLK2: J6.2, U7.22 (PA14/SWCLK)
SWDIO1: J3.1, U1.21 (PA13/SWDIO)
SWDIO2: J6.1, U7.21 (PA13/SWDIO)
VAA1: C12.1, C13.1, C14.1, D1.2 (A), D2.2 (A), D3.2 (A), D4.2 (A), D5.2 (A), D6.2 (A), D7.2 (A), D8.2 (A), D9.2 (A), D10.2 (A), D11.2 (A), D12.2 (A), D13.2 (A), D14.2 (A), D15.2 (A), D16.2 (A), D17.2 (A), D18.2 (A), Q2.3 (D), R4.1, R11.1, R13.1, R14.1, U3.2 (AD), U3.3 (VCC), U6.4 (VDD)
VAA2: C27.1, C28.1, C29.1, D20.2 (A), D21.2 (A), D22.2 (A), D23.2 (A), D24.2 (A), D25.2 (A), D26.2 (A), D27.2 (A), D28.2 (A), D29.2 (A), D30.2 (A), D31.2 (A), D32.2 (A), D33.2 (A), D34.2 (A), D35.2 (A), D36.2 (A), D37.2 (A), Q4.3 (D), R19.1, R26.1, R28.1, R29.1, U9.2 (AD), U9.3 (VCC), U12.4 (VDD)
VDD1: SW3.1 (A), U2.3 (EN), U2.4 (VIN)
VDD2: SW6.1 (A), U8.3 (EN), U8.4 (VIN)

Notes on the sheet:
TODOS/FIXES: - [ ] Add Hole in Paste Layer for Toolholes??? - bauteilnamen (1uF fehlt statt 8x2.2uF) - leds wieder auf 0603? - leichtere knöpfe -batterieladen checken - vllt kleineres steckerloch - text, grafik drauf
Microphone + Filter
Adapt Speaker PWM to OD Fix VDD switch for peripherals add caps?
leds
User Buzzer
Bat. Volt. Sense
Use internal OPA
Battery/Power Managment
LED + Driver
MCU
Aux. Device Power Mgmt.
I2C Pullup
User Push Buttons
15mA
for chips
Pogo Pads
Power Rail Decoupling
